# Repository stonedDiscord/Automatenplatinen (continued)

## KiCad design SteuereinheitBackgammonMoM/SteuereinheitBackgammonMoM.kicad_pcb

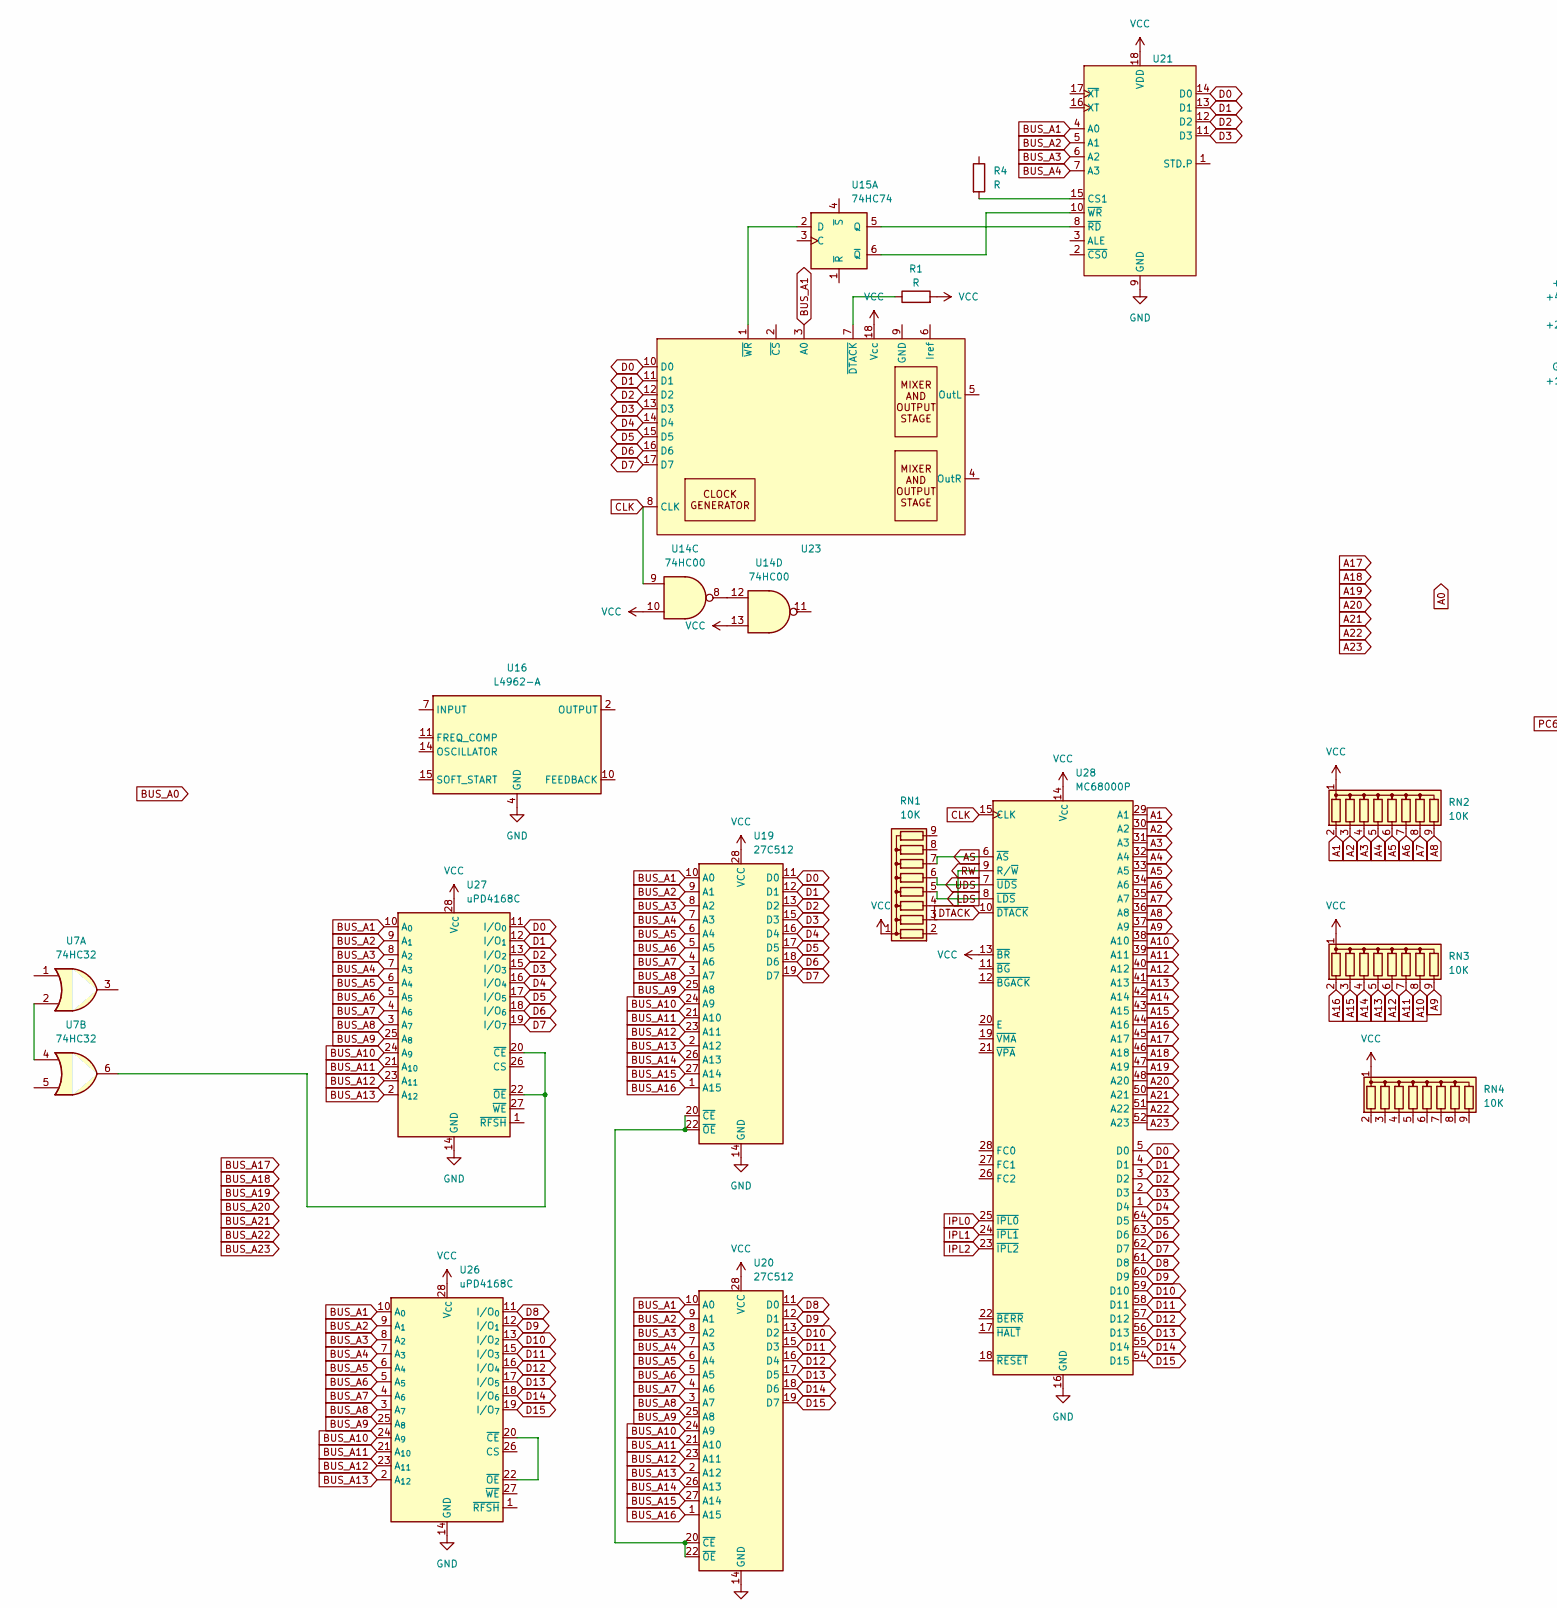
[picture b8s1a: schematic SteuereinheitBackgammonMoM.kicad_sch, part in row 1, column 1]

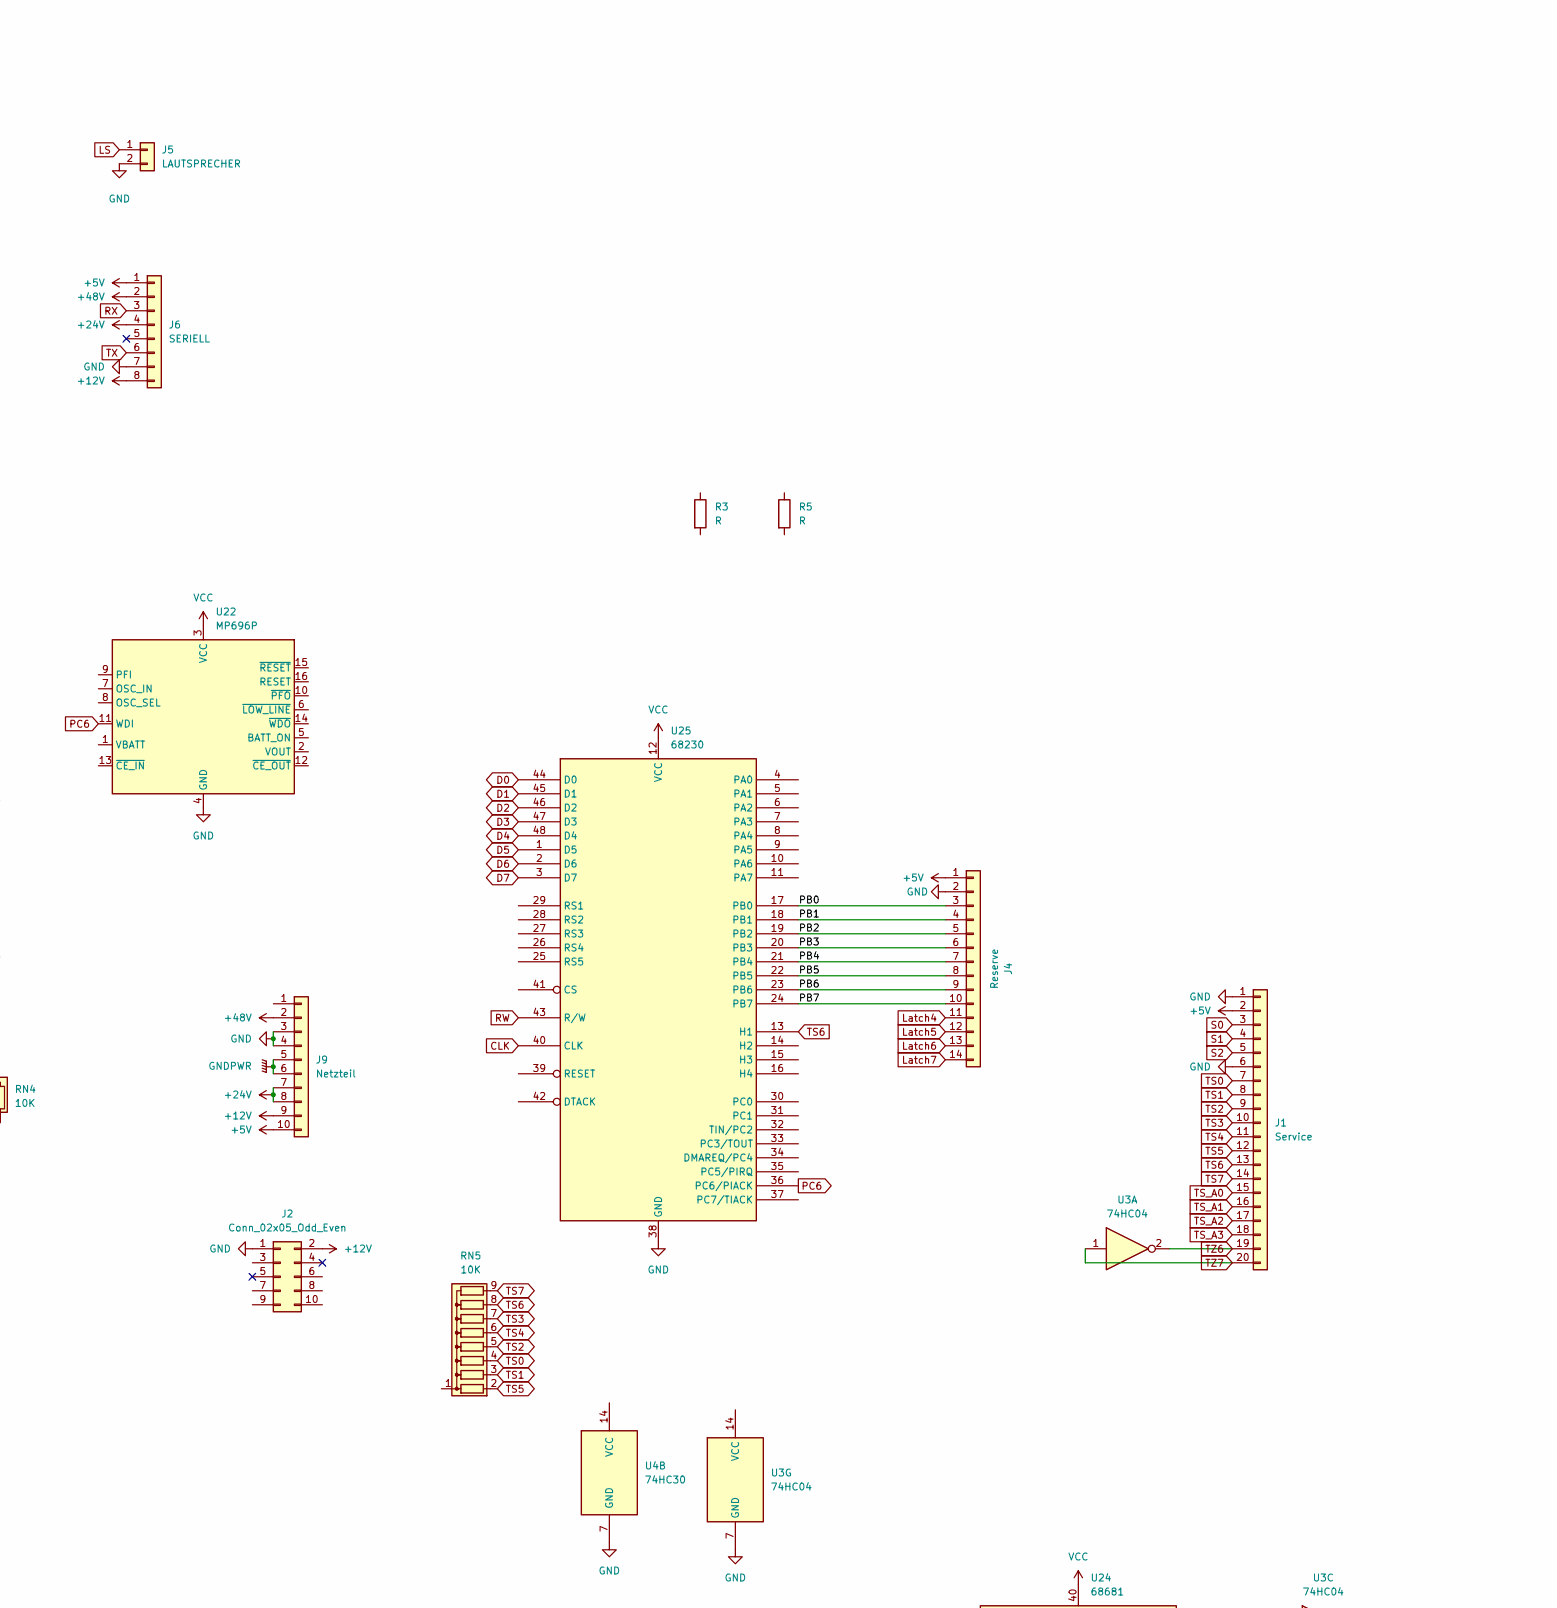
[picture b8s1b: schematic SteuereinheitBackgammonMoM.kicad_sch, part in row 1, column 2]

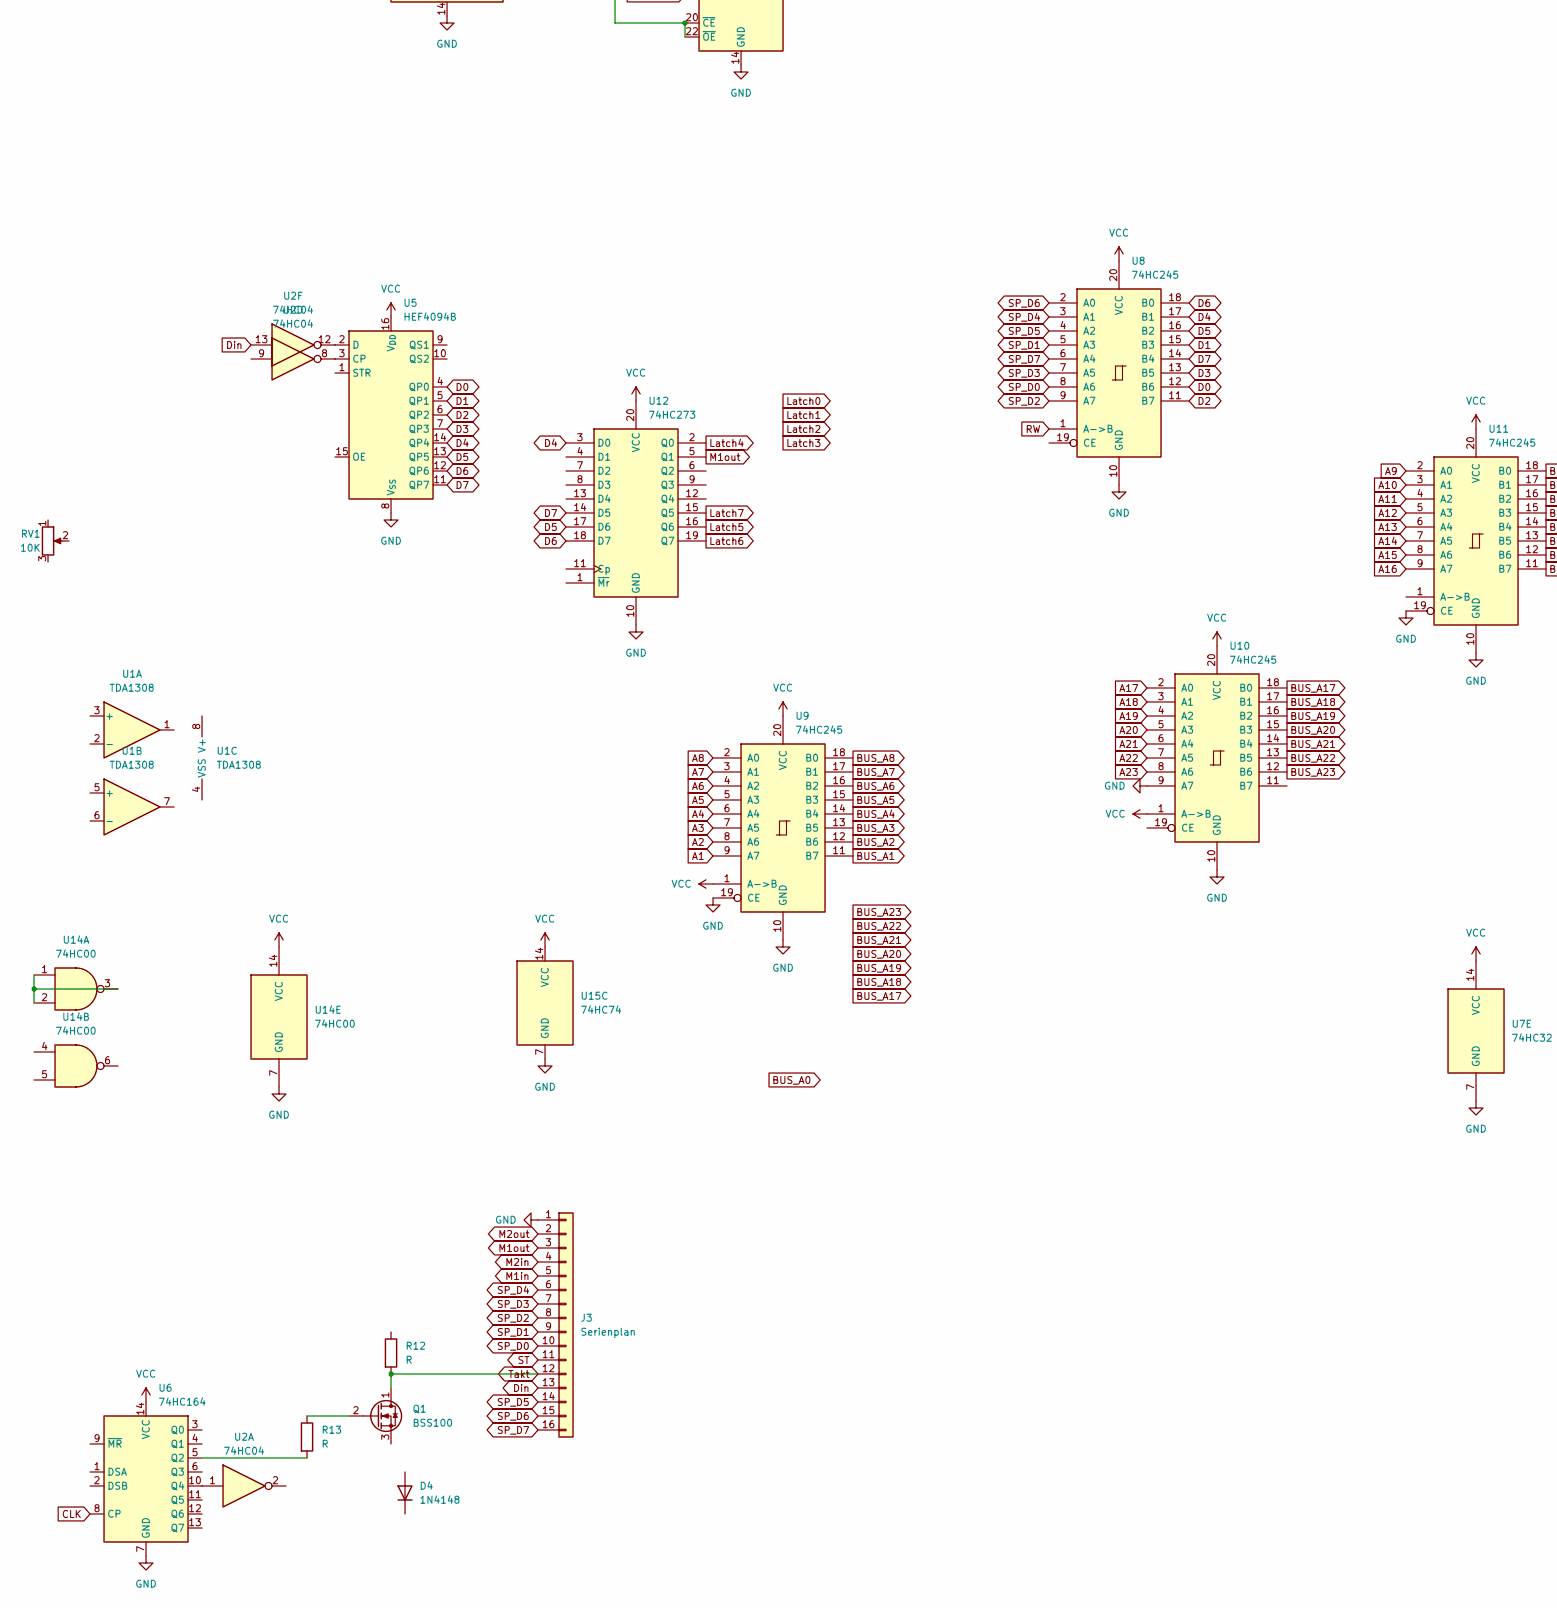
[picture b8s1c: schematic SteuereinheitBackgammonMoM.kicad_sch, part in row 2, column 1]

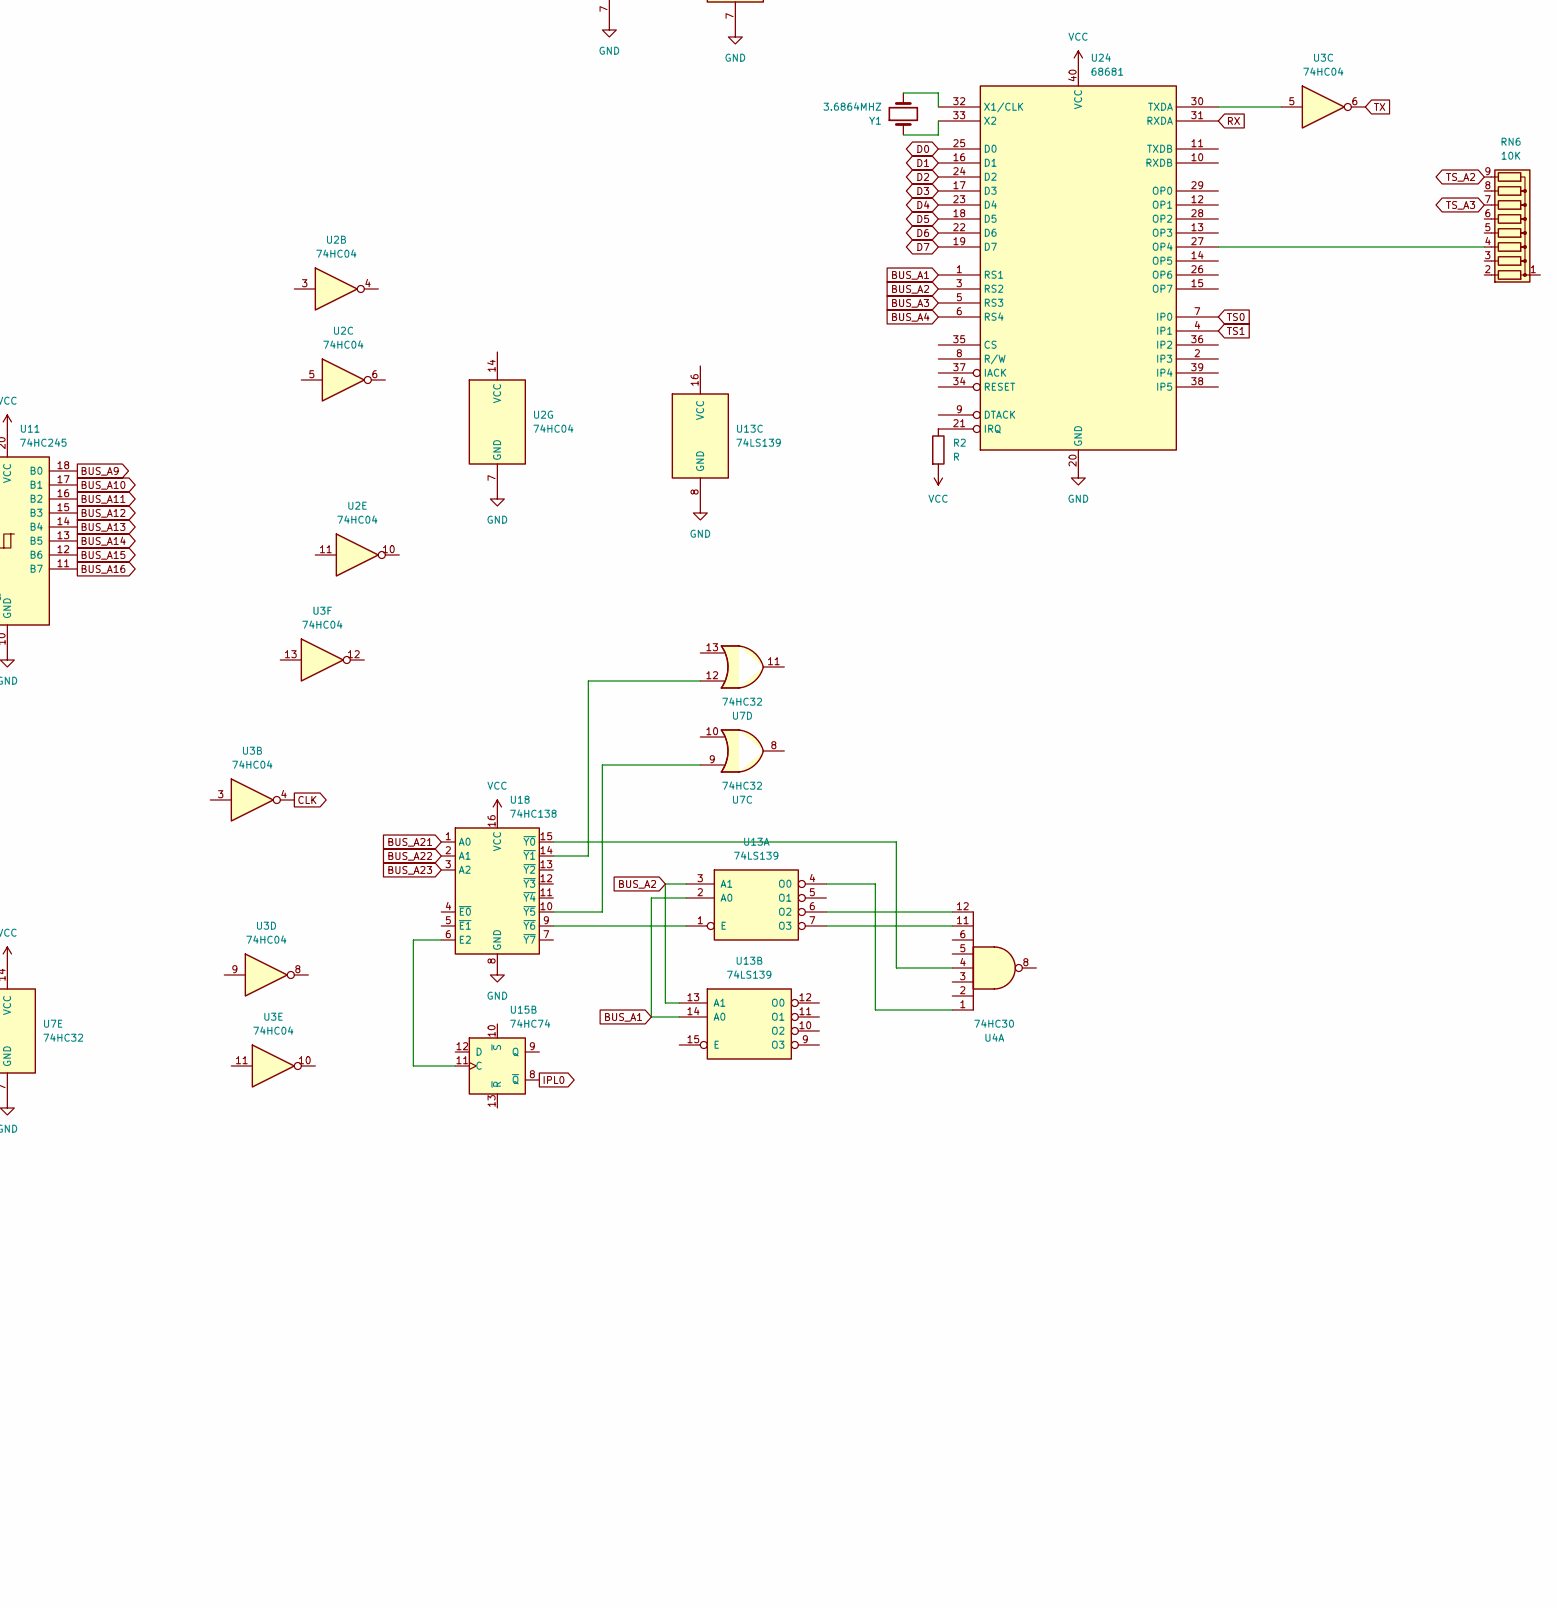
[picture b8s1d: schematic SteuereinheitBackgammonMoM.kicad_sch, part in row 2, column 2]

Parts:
D4: 1N4148; D_DO-35_SOD27_P7.62mm_Horizontal
J1: Service; Stocko_MKS_1670-6-0-2020_1x20_P2.50mm_Vertical
J2: Conn_02x05_Odd_Even; IDC-Header_2x05_P2.54mm_Vertical
J3: Serienplan; Stocko_MKS_1666-6-0-1616_1x16_P2.50mm_Vertical
J4: Reserve; Stocko_MKS_1664-6-0-1414_1x14_P2.50mm_Vertical
J5: LAUTSPRECHER; Stocko_MKS_1652-6-0-202_1x2_P2.50mm_Vertical
J6: SERIELL; Stocko_MKS_1658-6-0-808_1x8_P2.50mm_Vertical
J9: Netzteil; Stocko_MKS_1660-6-0-1010_1x10_P2.50mm_Vertical
Q1: BSS100; TO-92
R1, R2, R3, R4, R5, R12, R13: R; R_Axial_DIN0207_L6.3mm_D2.5mm_P10.16mm_Horizontal
RN1, RN2, RN3, RN4, RN5, RN6: 10K; R_Array_SIP9
RV1: 10K; Potentiometer_Piher_PT-10-V10_Vertical
U1: TDA1308
U2, U3: 74HC04; DIP-14_W7.62mm
U4: 74HC30; DIP-14_W7.62mm
U5: HEF4094B; DIP-16_W7.62mm
U6: 74HC164; DIP-14_W7.62mm
U7: 74HC32; DIP-14_W7.62mm
U8, U9, U10, U11: 74HC245; DIP-20_W7.62mm
U12: 74HC273; DIP-20_W7.62mm
U13: 74LS139; DIP-16_W7.62mm
U14: 74HC00; DIP-14_W7.62mm
U15: 74HC74; DIP-14_W7.62mm
U16: L4962-A; DIP-16_W7.62mm
U18: 74HC138; DIP-16_W7.62mm
U19, U20: 27C512; DIP-28_W15.24mm
U21, U23: DIP-18_W7.62mm
U22: MP696P; DIP-16_W7.62mm
U24: 68681; DIP-40_W15.24mm
U25: 68230; DIP-48_W15.24mm
U26, U27: uPD4168C; DIP-28_W15.24mm
U28: MC68000P; DIP-64_W22.86mm
Y1: 3.6864MHZ; Crystal_HC49-4H_Vertical

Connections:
+5V: J1.2, J4.1, J6.1, J9.10
+12V: J2.2, J6.8, J9.9
+24V: J6.4, J9.7, J9.8
+48V: J6.2, J9.2
/PB0: J4.3, U25.17 (PB0)
/PB1: J4.4, U25.18 (PB1)
/PB2: J4.5, U25.19 (PB2)
/PB3: J4.6, U25.20 (PB3)
/PB4: J4.7, U25.21 (PB4)
/PB5: J4.8, U25.22 (PB5)
/PB6: J4.9, U25.23 (PB6)
/PB7: J4.10, U25.24 (PB7)
A1: RN2.2 (R1), U9.9 (A7), U28.29 (A1)
A2: RN2.3 (R2), U9.8 (A6), U28.30 (A2)
A3: RN2.4 (R3), U9.7 (A5), U28.31 (A3)
A4: RN2.5 (R4), U9.6 (A4), U28.32 (A4)
A5: RN2.6 (R5), U9.5 (A3), U28.33 (A5)
A6: RN2.7 (R6), U9.4 (A2), U28.34 (A6)
A7: RN2.8 (R7), U9.3 (A1), U28.35 (A7)
A8: RN2.9 (R8), U9.2 (A0), U28.36 (A8)
A9: RN3.9 (R8), U11.2 (A0), U28.37 (A9)
A10: RN3.8 (R7), U11.3 (A1), U28.38 (A10)
A11: RN3.7 (R6), U11.4 (A2), U28.39 (A11)
A12: RN3.6 (R5), U11.5 (A3), U28.40 (A12)
A13: RN3.5 (R4), U11.6 (A4), U28.41 (A13)
A14: RN3.4 (R3), U11.7 (A5), U28.42 (A14)
A15: RN3.3 (R2), U11.8 (A6), U28.43 (A15)
A16: RN3.2 (R1), U11.9 (A7), U28.44 (A16)
A17: U10.2 (A0), U28.45 (A17)
A18: U10.3 (A1), U28.46 (A18)
A19: U10.4 (A2), U28.47 (A19)
A20: U10.5 (A3), U28.48 (A20)
A21: U10.6 (A4), U28.50 (A21)
A22: U10.7 (A5), U28.51 (A22)
A23: U10.8 (A6), U28.52 (A23)
AS: RN1.7 (R6), U28.6 (~AS)
BUS_A1: U9.11 (B7), U13.2 (A0), U13.14 (A0), U19.10 (A0), U20.10 (A0), U21.4 (A0), U23.3 (A0), U24.1 (RS1), U26.10 (A_{0}), U27.10 (A_{0})
BUS_A2: U9.12 (B6), U13.3 (A1), U13.13 (A1), U19.9 (A1), U20.9 (A1), U21.5 (A1), U24.3 (RS2), U26.9 (A_{1}), U27.9 (A_{1})
BUS_A3: U9.13 (B5), U19.8 (A2), U20.8 (A2), U21.6 (A2), U24.5 (RS3), U26.8 (A_{2}), U27.8 (A_{2})
BUS_A4: U9.14 (B4), U19.7 (A3), U20.7 (A3), U21.7 (A3), U24.6 (RS4), U26.7 (A_{3}), U27.7 (A_{3})
BUS_A5: U9.15 (B3), U19.6 (A4), U20.6 (A4), U26.6 (A_{4}), U27.6 (A_{4})
BUS_A6: U9.16 (B2), U19.5 (A5), U20.5 (A5), U26.5 (A_{5}), U27.5 (A_{5})
BUS_A7: U9.17 (B1), U19.4 (A6), U20.4 (A6), U26.4 (A_{6}), U27.4 (A_{6})
BUS_A8: U9.18 (B0), U19.3 (A7), U20.3 (A7), U26.3 (A_{7}), U27.3 (A_{7})
BUS_A9: U11.18 (B0), U19.25 (A8), U20.25 (A8), U26.25 (A_{8}), U27.25 (A_{8})
BUS_A10: U11.17 (B1), U19.24 (A9), U20.24 (A9), U26.24 (A_{9}), U27.24 (A_{9})
BUS_A11: U11.16 (B2), U19.21 (A10), U20.21 (A10), U26.21 (A_{10}), U27.21 (A_{10})
BUS_A12: U11.15 (B3), U19.23 (A11), U20.23 (A11), U26.23 (A_{11}), U27.23 (A_{11})
BUS_A13: U11.14 (B4), U19.2 (A12), U20.2 (A12), U26.2 (A_{12}), U27.2 (A_{12})
BUS_A14: U11.13 (B5), U19.26 (A13), U20.26 (A13)
BUS_A15: U11.12 (B6), U19.27 (A14), U20.27 (A14)
BUS_A16: U11.11 (B7), U19.1 (A15), U20.1 (A15)
BUS_A17: U10.18 (B0)
BUS_A18: U10.17 (B1)
BUS_A19: U10.16 (B2)
BUS_A20: U10.15 (B3)
BUS_A21: U10.14 (B4), U18.1 (A0)
BUS_A22: U10.13 (B5), U18.2 (A1)
BUS_A23: U10.12 (B6), U18.3 (A2)
CLK: U3.4, U6.8 (CP), U14.9, U23.8 (CLK), U25.40 (CLK), U28.15 (CLK)
D0: U5.4 (QP0), U8.12 (B6), U19.11 (D0), U21.14 (D0), U23.10 (D0), U24.25 (D0), U25.44 (D0), U27.11 (I/O_{0}), U28.5 (D0)
D1: U5.5 (QP1), U8.15 (B3), U19.12 (D1), U21.13 (D1), U23.11 (D1), U24.16 (D1), U25.45 (D1), U27.12 (I/O_{1}), U28.4 (D1)
D2: U5.6 (QP2), U8.11 (B7), U19.13 (D2), U21.12 (D2), U23.12 (D2), U24.24 (D2), U25.46 (D2), U27.13 (I/O_{2}), U28.3 (D2)
D3: U5.7 (QP3), U8.13 (B5), U19.15 (D3), U21.11 (D3), U23.13 (D3), U24.17 (D3), U25.47 (D3), U27.15 (I/O_{3}), U28.2 (D3)
D4: U5.14 (QP4), U8.17 (B1), U12.3 (D0), U19.16 (D4), U23.14 (D4), U24.23 (D4), U25.48 (D4), U27.16 (I/O_{4}), U28.1 (D4)
D5: U5.13 (QP5), U8.16 (B2), U12.17 (D6), U19.17 (D5), U23.15 (D5), U24.18 (D5), U25.1 (D5), U27.17 (I/O_{5}), U28.64 (D5)
D6: U5.12 (QP6), U8.18 (B0), U12.18 (D7), U19.18 (D6), U23.16 (D6), U24.22 (D6), U25.2 (D6), U27.18 (I/O_{6}), U28.63 (D6)
D7: U5.11 (QP7), U8.14 (B4), U12.14 (D5), U19.19 (D7), U23.17 (D7), U24.19 (D7), U25.3 (D7), U27.19 (I/O_{7}), U28.62 (D7)
D8: U20.11 (D0), U26.11 (I/O_{0}), U28.61 (D8)
D9: U20.12 (D1), U26.12 (I/O_{1}), U28.60 (D9)
D10: U20.13 (D2), U26.13 (I/O_{2}), U28.59 (D10)
D11: U20.15 (D3), U26.15 (I/O_{3}), U28.58 (D11)
D12: U20.16 (D4), U26.16 (I/O_{4}), U28.57 (D12)
D13: U20.17 (D5), U26.17 (I/O_{5}), U28.56 (D13)
D14: U20.18 (D6), U26.18 (I/O_{6}), U28.55 (D14)
D15: U20.19 (D7), U26.19 (I/O_{7}), U28.54 (D15)
DTACK: U28.10 (~DTACK)
Din: J3.13, U2.13
GND: J1.1, J1.6, J2.1, J3.1, J4.2, J5.2, J6.7, J9.3, J9.4, U2.7 (GND_7), U3.7 (GND_7), U4.7 (GND_7), U5.8 (V_{SS}), U6.7 (GND), U7.7 (GND), U8.10 (GND), U9.10 (GND), U9.19 (CE), U10.9 (A7), U10.10 (GND), U11.10 (GND), U11.19 (CE), U12.10 (GND), U13.8 (GND), U14.7 (GND), U15.7 (GND), U16.4 (GND), U16.5 (GND), U16.12 (GND), U16.13 (GND), U18.8 (GND), U19.14 (GND), U20.14 (GND), U21.9 (GND), U22.4 (GND), U24.20 (GND), U25.38 (GND), U26.14 (GND), U27.14 (GND), U28.16 (GND), U28.53 (GND)
GNDPWR: J9.5, J9.6
IPL0: U15.8 (~Q), U28.25 (~IPL0)
IPL1: U28.24 (~IPL1)
IPL2: U28.23 (~IPL2)
LDS: RN1.5 (R4), U28.8 (~LDS)
LS: J5.1
Latch4: J4.11, U12.2 (Q0)
Latch5: J4.12, U12.16 (Q6)
Latch6: J4.13, U12.19 (Q7)
Latch7: J4.14, U12.15 (Q5)
M1in: J3.5
M1out: J3.3, U12.5 (Q1)
M2in: J3.4
M2out: J3.2
unnamed: Q1.2 (G), R13.1
unnamed: RN6.4 (R3), U24.27 (OP4)
unnamed: U2.8, U5.3 (CP)
unnamed: U2.12, U5.2 (D)
unnamed: R13.2, U6.5 (Q2)
unnamed: U2.1, U6.10 (Q4)
unnamed: U7.2, U7.4
unnamed: U13.1 (E), U18.9 (~Y6)
unnamed: U4.1, U13.4 (O0)
unnamed: U4.12, U13.6 (O2)
unnamed: U4.11, U13.7 (O3)
unnamed: U14.1, U14.2, U14.3
unnamed: U14.8, U14.12
unnamed: U15.2 (D), U23.1 (~WR)
unnamed: U15.5 (Q), U21.8 (~RD)
unnamed: U15.6 (~Q), U21.10 (~WR)
unnamed: U15.11 (C), U18.6 (E2)
unnamed: U4.4, U18.15 (~Y0)
unnamed: U7.12, U18.14 (~Y1)
unnamed: U7.9, U18.10 (~Y5)
unnamed: U19.20 (~CE), U19.22 (~OE), U20.20 (~CE), U20.22 (~OE)
unnamed: R4.2, U21.15 (CS1)
unnamed: R1.1, U23.7 (~DTACK)
unnamed: R2.1, U24.21 (IRQ)
unnamed: U3.5, U24.30 (TXDA)
unnamed: U24.32 (X1/CLK), Y1.2
unnamed: U24.33 (X2), Y1.1
unnamed: U26.20 (~CE), U26.22 (~OE)
unnamed: U7.6, U27.20 (~CE), U27.22 (~OE)
PC6: U22.11 (WDI), U25.36 (PC6/PIACK)
RW: RN1.4 (R3), U8.1 (A->B), U25.43 (R/W), U28.9 (R/~W)
RX: J6.3, U24.31 (RXDA)
S0: J1.3
S1: J1.4
S2: J1.5
SP_D0: J3.10, U8.8 (A6)
SP_D1: J3.9, U8.5 (A3)
SP_D2: J3.8, U8.9 (A7)
SP_D3: J3.7, U8.7 (A5)
SP_D4: J3.6, U8.3 (A1)
SP_D5: J3.14, U8.4 (A2)
SP_D6: J3.15, U8.2 (A0)
SP_D7: J3.16, U8.6 (A4)
ST: J3.11
TS0: J1.7, RN5.4 (R3), U24.7 (IP0)
TS1: J1.8, RN5.3 (R2), U24.4 (IP1)
TS2: J1.9, RN5.5 (R4)
TS3: J1.10, RN5.7 (R6)
TS4: J1.11, RN5.6 (R5)
TS5: J1.12, RN5.2 (R1)
TS6: J1.13, RN5.8 (R7), U25.13 (H1)
TS7: J1.14, RN5.9 (R8)
TS_A0: J1.15
TS_A1: J1.16
TS_A2: J1.17, RN6.9 (R8)
TS_A3: J1.18, RN6.7 (R6)
TX: J6.6, U3.6
TZ6: J1.19, U3.2
TZ7: J1.20, U3.1
Takt: J3.12, Q1.1 (D), R12.2
UDS: RN1.6 (R5), U28.7 (~UDS)
VCC: R1.2, R2.2, RN1.1 (common), RN2.1 (common), RN3.1 (common), RN4.1 (common_1), U5.16 (V_{DD}), U6.14 (VCC), U7.14 (VCC), U8.20 (VCC), U9.1 (A->B), U9.20 (VCC), U10.1 (A->B), U10.20 (VCC), U11.20 (VCC), U12.20 (VCC), U14.10, U14.13, U14.14 (VCC), U15.14 (VCC), U18.16 (VCC), U19.28 (VCC), U20.28 (VCC), U21.18 (VDD), U22.3 (VCC), U23.18 (Vcc), U24.40 (VCC), U25.12 (VCC), U26.28 (V_{CC}), U27.28 (V_{CC}), U28.13 (~BR), U28.14 (V_{CC}), U28.49 (V_{CC})

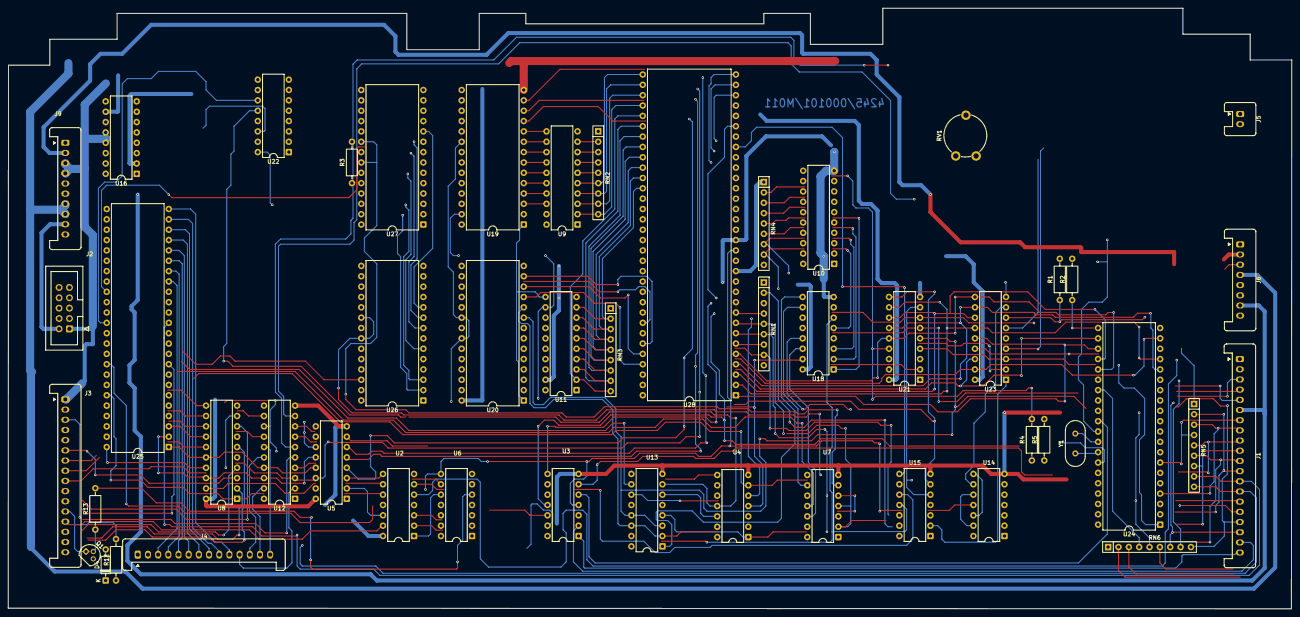
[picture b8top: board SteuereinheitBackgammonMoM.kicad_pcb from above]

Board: 2 copper layers, 315.0 x 147.4 mm, 50 parts (0 on the bottom side), 138 nets.

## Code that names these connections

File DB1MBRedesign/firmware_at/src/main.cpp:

#include <avr/io.h>
#include <util/delay.h>
#include <stdbool.h>
#include <avr/interrupt.h>
#include <avr/sleep.h>
#include <avr/wdt.h>
#include <avr/eeprom.h>

#include "bdm.h"
#include "rtc.h"

#include "mc68331.h"

/* 
 * PIN MAPPINGS
 * ----------------------------------
 * RTC4543SB:
 *   CLK:  PB5, DATA: PC4, CE: PB1, WR: PB3
 *
 * TARGET (BDM Device):
 *   DSCLK: PC0, DSI: PC3, DSO: PD6
 *
 * INTRUSION:
 *   PROBE: PB1 (Pulsed), SENSE: PD5 (T1 Input)
 */

// System state machine
typedef enum {
    STATE_IDLE      = 0x01,
    STATE_INTRUSION = 0x02,
    STATE_ACTIVE    = 0x03
} system_state_t;

volatile system_state_t g_state = STATE_IDLE;

// ============================================================================
// Intrusion detection
// ============================================================================

uint8_t check_intrusion() {
    // Stop and reset Timer1
    TCCR1B = 0;
    TCNT1 = 0;
    
    // Pulse PB1 (probe)
    PORTB |= (1 << PB1);
    _delay_us(10);
    PORTB &= ~(1 << PB1);
    
    // Timer1: external clock on T1 (PD5), rising edge
    TCCR1B = (1 << CS12) | (1 << CS11);  // External clock source
    
    // Software delay while timer counts external pulses on PD5
    for (volatile uint16_t i = 7999; i > 0; i--);
    
    TCCR1B = 0;  // Stop timer
    // Firmware: return 1 if TCNT1 >= 0x15
    return (TCNT1 >= 0x15) ? 1 : 0;
}

// ============================================================================
// Target MC68331 initialization
// ============================================================================

void target_init() {
    // Initialize CPU32 core registers
    bdm_write_word(SIMCR,  0x40CF);
    bdm_write_word(SYNCR,  0x7F03);
    _delay_ms(20);
    bdm_write_word(SYPCR,  0x004C);
    bdm_write_word(CSPAR0, 0x3FFF);
    bdm_write_word(CSPAR1, 0x03FD);
    bdm_write_word(CSBARBT, 0x0007);
    bdm_write_word(CSORBT,  0x6C70);
    bdm_write_word(CSBAR0, 0x0007);
    bdm_write_word(CSOR0,  0x7470);
    bdm_write_word(CSBAR1, 0x0007);
    bdm_write_word(CSOR1,  0x7070);
    bdm_write_word(CSBAR2, 0x0007);
    bdm_write_word(CSOR2,  0x7070);
    
    // Load EEPROM contents to target RAM at 0x3C0 (0x40 words)
    for (uint16_t addr = 0x0000; addr < 0x0040; addr += 2) {
        uint16_t data = eeprom_read_word((uint16_t*)addr);
        bdm_write_word(0x03C0 + addr, data);
    }
    
    // NOTE: Firmware performs additional BDM register writes after EEPROM load
    // (peripheral/timer/UART configuration). TODO
}

// ============================================================================
// Timer2 Compare A ISR – main power‑management / state machine
// ============================================================================

ISR(TIMER2_COMPA_vect) {
    switch (g_state) {
        case STATE_IDLE:
            if (check_intrusion()) {
                g_state = STATE_INTRUSION;
            }
            // Else remain idle – will sleep again
            break;
            
        case STATE_INTRUSION:
            target_init();
            g_state = STATE_ACTIVE;
            break;
            
        case STATE_ACTIVE:
            if (!check_intrusion()) {
                g_state = STATE_IDLE;
            }
            // Long processing delay (~1.6 s) as in firmware
            for (volatile uint32_t i = 1599999; i > 0; i--);
            break;
            
        default:
            g_state = STATE_IDLE;
            break;
    }
}

// ============================================================================
// TIMER0_COMPA ISR – not used; firmware redirects all ints here
// ============================================================================

ISR(TIMER0_COMPA_vect) {
    // Firmware's interrupt vectors for INT0‑7, PCINT, WDT all rjmp to RESET.
    // Empty ISR prevents unwanted resets if accidentally enabled.
}

ISR(TIMER1_COMPA_vect) {
    // Firmware redirects this vector to TIMER0_COMPA. Keep empty.
}

// ============================================================================
// Hardware initialization
// ============================================================================

void system_init() {
    cli();
    
    // Disable watchdog
    wdt_reset();
    WDTCSR |= (1 << WDCE) | (1 << WDE);
    WDTCSR = 0x00;
    
    // Power reduction: turn off unused modules (firmware: PRR=0xAE)
    PRR = 0xAE;
    
    // Digital input disable: disable buffers on ADC/T1 pins
    DIDR0 = 0x2E;
    DIDR1 = 0x02;
    
    // Pin directions (per firmware)
    DDRB |= (1 << PB1) | (1 << PB3) | (1 << PB5);  // RTC CE/WR/CLK outputs
    DDRC |= (1 << PC0) | (1 << PC3);               // BDM DSCLK/DSI outputs
    DDRC &= ~(1 << PC4);                            // RTC DATA input
    DDRD &= ~((1 << PD4) | (1 << PD5) | (1 << PD6)); // Intrusion sense, BDM DSO inputs
    
    // Pull-ups: BDM lines idle high
    PORTC |= (1 << PC0) | (1 << PC3);
    
    // Timer1: stopped; configured in check_intrusion() for ext clock on PD5/T1
    TCCR1A = 0;
    TCCR1B = 0;
    TCCR1C = 0;
    
    // Timer2: async mode, external 32.768 kHz crystal
    // ASSR.AS2=1, TCCR2B:CS22:CS21=11 (ext clock, falling edge), OCR2A=0
    ASSR = (1 << AS2);
    TCCR2A = 0x00;
    TCCR2B = (1 << CS22) | (1 << CS21);
    OCR2A = 0;
    TCNT2 = 0;
    
    // Wait for async registers to synchronize
    while (ASSR & ((1 << TCN2UB) | (1 << OCR2AUB) | (1 << TCR2BUB)));
    
    // Clear Timer2 Compare A flag and enable interrupt
    TIFR2 = (1 << OCF2A);
    TIMSK2 = (1 << OCIE2A);
    
    sei();  // Global interrupt enable
}

// ============================================================================
// Main entry point
// ============================================================================

int main() {
    system_init();
    
    // Read RTC to clear shift register (double-read per firmware)
    uint8_t rtc_buf[7];
    rtc_4543_read(rtc_buf);
    rtc_4543_read(rtc_buf);
    
    g_state = STATE_IDLE;
    
    while (1) {
        if (g_state == STATE_IDLE) {
            // Sleep until Timer2 Compare A wakes the CPU
            set_sleep_mode(SLEEP_MODE_PWR_DOWN);
            sleep_mode();
            // On wake, ISR will handle state transition
        }
        else if (g_state == STATE_INTRUSION) {
            target_init();
            g_state = STATE_ACTIVE;
        }
        else if (g_state == STATE_ACTIVE) {
            if (!check_intrusion()) {
                g_state = STATE_IDLE;
            }
            // Long delay mimicking firmware loop
            for (volatile uint32_t i = 1599999; i > 0; i--);
        }
        else {
            g_state = STATE_IDLE;
        }
    }
}

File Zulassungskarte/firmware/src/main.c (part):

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
// --- Configuration ---

#define MOSI_PIN PB3
#define MISO_PIN PB4
#define SCK_PIN  PB5

// Command codes received from SPI Master
enum Command {
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// --- Crypto Operations ---

static uint8_t transform_byte_a(uint8_t val) {
    uint8_t res = 0;
    uint8_t mask = 0x25;
    for (uint8_t i = 0; i < 8; i++) {
        res <<= 1;
        if (mask & 0x80) res += val;
        mask <<= 1;
    }
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}

static uint8_t transform_byte_b(uint8_t val) {
    uint8_t res = 0;
    uint8_t mask = 0xAD;
    for (uint8_t i = 0; i < 8; i++) {
        res <<= 1;
        if (mask & 0x80) res += val;
        mask <<= 1;
    }
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    PORTD = 0;
    PORTC = 0;
    PORTB = 0;
    DDRB = 0xF7; // PB3 (MOSI) as input, others as output

    // Watchdog Setup
    WDTCSR |= (1 << WDCE) | (1 << WDE);
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
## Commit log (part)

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2025-03-09 werte
2025-03-11 cap werte
2025-03-13 ausles
2025-03-13 lampe
2025-03-13 taster
2025-03-13 pins
2025-03-13 taster LED
2025-03-13 zlk alt
2025-03-14 silkscreen, parts
2025-03-14 rueckseite maske
2025-03-14 aussparung
2025-03-14 cleanup
2025-03-14 arduino isp und anschluss der normal am halter ist
2025-03-15 fehler weg
2025-03-17 st25 tastatur
2025-03-17 nsm adapterplatine unterseite
2025-03-18 5v und loecher
2025-03-18 kleinerer sim kontakt
2025-03-19 komplett? muss ich noch pruefen
2025-03-19 bally hat die kontakte anders rum
2025-03-20 led und ffc
2025-03-20 loecher dann doch
2025-03-20 eckendeckel
2025-03-20 deckel sonne
2025-03-20 beschriftung hinten
2025-03-21 halbzeit
2025-03-22 rev1
2025-03-23 zweite reihe
2025-03-23 stromleitungen
2025-03-23 beschriftung
2025-03-24 st25 tastatur gerber
2025-03-25 kicad 9 update
2025-03-25 DATENBANK
2025-03-25 loch
2025-03-26 klassik
2025-03-26 direkt adapter
2025-03-28 kicad9 update
2025-03-29 gleichrichter
2025-03-29 kleine lampe
2025-03-29 taster gerber
2025-03-29 halter gerber
2025-03-30 jumper
2025-04-01 programmierboard bis auf 2 linien
2025-04-01 vnd10bsp
2025-04-02 gehäuse schrott
2025-04-02 emp mit foto
2025-04-03 schalplan
2025-04-03 export
2025-04-03 noch eine tastatur
2025-04-03 schaltplan
2025-04-07 vias
2025-04-10 widerstand
2025-04-10 more buttons
2025-04-10 power
2025-04-10 inner
2025-04-11 stifte nach vorne wegen dem hebel
2025-04-15 12v zlk
2025-04-24 spannungs messung
2025-04-29 language tag
2025-04-29 kontaktinfos
2025-04-29 bilder raus
2025-04-29 zlk widerstand
2025-04-29 rumgeschiebe
2025-05-02 sprache
2025-05-02 drecks plugin
2025-05-05 rechtschreibung
2025-05-05 formulierung
2025-05-05 spannung aus dem kopf
2025-05-06 station text
2025-05-07 triple16
2025-05-08 ausgabe von 3d
2025-05-08 roentgen
2025-05-09 unterseite scan
2025-05-13 bilder weg
2025-05-13 kondensatoren
2025-05-13 text verschoben
2025-05-19 funnyled
2025-06-03 usbasp stecker
2025-06-04 komponenten werte
2025-06-06 kondensator fehlte
2025-06-07 oberseite
2025-06-09 ZLK software
2025-06-09 eeprom
2025-06-09 autodetect cpu
2025-06-16 25.2
2025-06-16 halbe miete
2025-06-24 xray
2025-06-24 no renders
2025-06-24 step files are copyright manufacturer
2025-06-24 chinaknopf
2025-06-26 testp
2025-06-28 aussen pins
2025-06-28 no more autodetect (didnt work)
2025-06-28 wieso war das da
2025-06-29 linie
2025-07-03 soundregler
2025-07-09 lampentreiber
2025-07-09 seite 1
2025-07-12 lampen
2025-07-12 vorcpu
2025-07-12 ncpu
2025-07-12 schlimmer wie vorher
2025-07-12 mode
2025-07-13 unterseite durch
2025-07-13 modul
2025-07-13 adapter
2025-07-13 modul2
2025-07-21 oben
2025-07-24 bw bilder
2025-07-24 modul atmega
2025-07-25 systemmodul fertig
2025-07-31 pin2
2025-08-08 fotos
2025-08-08 lumberg stecker
2025-08-11 hinweis lol
2025-08-16 einladung
2025-08-18 gitignore
2025-08-18 render
2025-08-20 knopf
2025-09-10 lamp refresh
2025-09-11 loader
2025-09-15 fidu
2025-09-16 led widerstand
2025-09-17 scan
2025-09-21 daten
2025-10-03 kran
2025-11-07 weg mit dem zeug
2025-11-28 512k
2025-11-29 systemmodul reset
2025-11-29 move board
2025-11-29 reset typ
2025-11-29 teilenummern
2025-12-06 tastatur adapter
2025-12-06 dicke fertig
2025-12-06 oki du ar
2025-12-06 gl label und q
2025-12-06 diode
2025-12-06 kompletti
2025-12-15 4017 beschriftung
2026-01-02 sussy
2026-01-02 move symbols
2026-01-02 epson rtc
2026-01-02 uPD70325
2026-01-02 move 2
2026-01-02 replies
2026-01-02 anleitung
2026-01-05 build script
2026-01-05 clown emoji
2026-01-05 init boot loader
2026-01-08 modclk
2026-01-09 bgnd
2026-01-14 neues bild
2026-01-17 greeeen
2026-01-20 3d export
2026-01-20 3d halter
2026-02-01 ste25
2026-02-11 net namen
2026-02-11 cpu und eprom
2026-02-11 lib table
2026-02-11 kleinigkeit
2026-02-11 nsm jumper
2026-02-11 zlk tag connect
2026-02-11 del alt
2026-02-11 untenrum fertig
2026-02-11 alles verbunden
2026-02-12 battok
2026-02-12 silkscreen
2026-02-16 bild
2026-02-16 onboard rom
2026-02-26 command
2026-02-26 connector
2026-02-26 display
2026-02-26 no error
2026-03-07 sus pins
2026-03-07 jamma adapter
2026-03-07 druckerport
2026-03-20 Create erc-drc.yml
    test
2026-03-20 1stern
2026-03-20 project matrix
2026-03-20 no fail fast
2026-03-20 report file
2026-03-20 list
2026-03-20 Kompakt
2026-03-20 fix jason
2026-03-20 archive is new
2026-03-20 either
2026-03-20 files instead
2026-03-20 names
2026-03-20 still run drc
2026-03-20 paths
2026-03-20 module
2026-03-20 step summary instead of artifact
2026-03-20 stop spam
2026-03-20 html tags
2026-03-21 ercdrc
2026-03-21 erc lamp
2026-03-21 war eh falsch
2026-03-21 zlk drc
2026-03-21 silk
2026-03-30 sus testpoint
2026-04-01 alt pins
2026-04-01 kicad 10
2026-04-01 match
2026-04-01 erc+drc
2026-04-02 sudo Update erc-drc.yml
2026-04-02 too good to be true
2026-04-02 print summary
2026-04-02 simpler
2026-04-02 500mb difference but comes with symbols
2026-04-02 global libraries
2026-04-02 theres no place like $HOME
2026-04-04 kicad 10 update
2026-04-04 finish board
2026-04-06 alles raus
2026-04-06 debugstation
2026-04-06 renata
2026-04-06 LEDs andersrum
2026-04-11 atmel test
2026-04-11 jamma pcb
2026-04-12 kicad10
2026-04-13 ende drucker und jamma unten
2026-04-13 sys25 erc
2026-04-13 batterie courtyard
2026-04-16 attempt
2026-04-17 gehäuse notiz
2026-04-17 anderes
2026-04-22 lader
2026-04-23 88pa
2026-04-24 lader bestellt
2026-04-24 station verkleinert
2026-04-26 move to header
2026-04-26 timers
2026-04-26 autoformat
2026-04-26 move rtc
2026-04-26 rename
2026-04-26 move addresses
2026-04-28 isp adapter
2026-04-28 zlk fw
2026-04-29 refactor
2026-04-29 rename to c
2026-04-29 ym oben
2026-04-29 spi command
2026-05-03 ele bom
2026-05-03 export script
2026-05-03 atmega order
2026-05-03 extra defines
2026-05-07 ym pins
2026-05-11 diagram
2026-05-11 fix footprints
2026-05-11 3d model and gnd fill top right
2026-05-11 warnings
2026-05-11 isp readme
2026-05-11 move to https://github.com/stonedDiscord/ArduinoISP
2026-05-11 soundkarte symbols
2026-05-11 zlk firmware template
2026-05-13 rom line
2026-05-13 videokarte m encoder
2026-05-13 zlk pio
2026-05-13 halter sid sod
2026-05-13 zl script
2026-05-13 pio config
2026-05-13 upload script
2026-05-13 split erc and drc
2026-05-13 gnu as
2026-05-13 b script
2026-05-13 bytes
2026-05-15 chips
2026-05-19 add msm
2026-05-19 doppelt
2026-05-19 aus der doku
2026-05-19 backg/manoman
2026-05-19 signalnamen
2026-05-20 kleiner
2026-05-20 intel
2026-05-24 strom
2026-05-24 rarr
2026-05-30 plsatik
